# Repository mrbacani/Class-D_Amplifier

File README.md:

# Class-D_Amplifier
Repository for a Class-D amplifier project

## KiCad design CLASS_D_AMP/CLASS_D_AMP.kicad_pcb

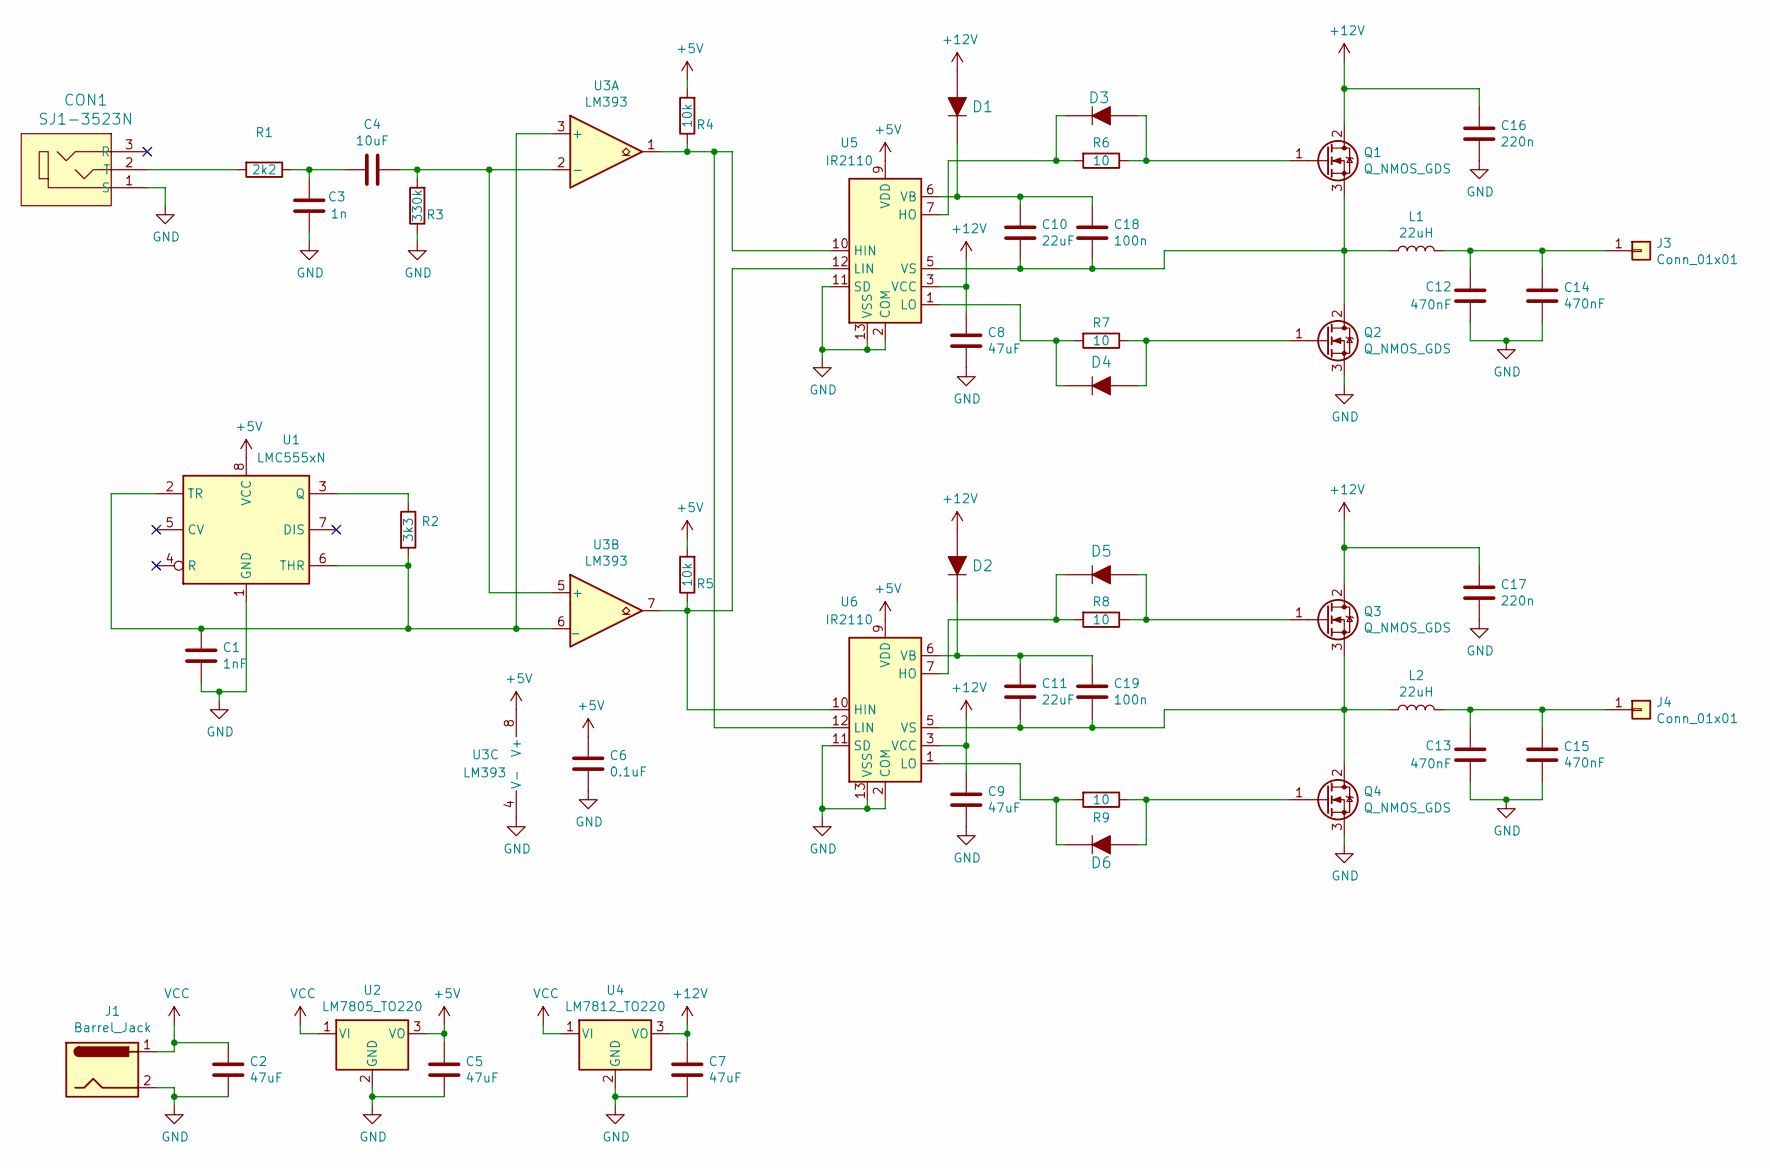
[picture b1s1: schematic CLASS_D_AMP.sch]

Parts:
C1: 1nF; C_1210_3225Metric_Pad1.33x2.70mm_HandSolder
C2, C5, C7, C8, C9: 47uF; C_1210_3225Metric_Pad1.33x2.70mm_HandSolder
C3: 1n; C_1210_3225Metric_Pad1.33x2.70mm_HandSolder
C4: 10uF; C_1210_3225Metric_Pad1.33x2.70mm_HandSolder
C6: 0.1uF; C_1210_3225Metric_Pad1.33x2.70mm_HandSolder
C10, C11: 22uF; C_1210_3225Metric_Pad1.33x2.70mm_HandSolder
C12, C13, C14, C15: 470nF; C_1210_3225Metric_Pad1.33x2.70mm_HandSolder
C16, C17: 220n; C_1210_3225Metric_Pad1.33x2.70mm_HandSolder
C18, C19: 100n; C_1210_3225Metric_Pad1.33x2.70mm_HandSolder
CON1: SJ1-3523N; Headphone_Jack_3.5mm_SJ1-3523N; MPN SJ1-3523N; Digi-Key_PN CP1-3523N-ND
D1, D2, D3, D4, D5, D6: 1N4148X-TP; SOD-523; MPN 1N4148X-TP; Digi-Key_PN 1N4148XTPMSCT-ND
J1: Barrel_Jack; Barrel_Jack_5.5mmODx2.1mmID_PJ-202A
J3, J4: Conn_01x01; PinHeader_1x01_P2.54mm_Vertical
L1, L2: 22uH; L_1210_3225Metric_Pad1.42x2.65mm_HandSolder
Q1, Q2, Q3, Q4: Q_NMOS_GDS; TO-220-3
R1: 2k2; R_1210_3225Metric_Pad1.30x2.65mm_HandSolder
R2: 3k3; R_1210_3225Metric_Pad1.30x2.65mm_HandSolder
R3: 330k; R_1210_3225Metric_Pad1.30x2.65mm_HandSolder
R4, R5: 10k; R_1210_3225Metric_Pad1.30x2.65mm_HandSolder
R6, R7, R8, R9: 10; R_1210_3225Metric_Pad1.30x2.65mm_HandSolder
U1: LMC555xN; DIP-8_W7.62mm
U2: LM7805_TO220; TO-220-3_Vertical
U3: LM393; SOIC-8_W3.9mm
U4: LM7812_TO220; TO-220-3_Vertical
U5, U6: IR2110; DIP-14_W7.62mm

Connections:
+5V: C5.1, C6.1, R4.2, R5.2, U1.8 (VCC), U2.3 (VO), U3.8 (V+), U5.9 (VDD), U6.9 (VDD)
+12V: C7.1, C8.1, C9.1, C16.1, C17.1, D1.A, D2.A, Q1.2 (D), Q3.2 (D), U4.3 (VO), U5.3 (VCC), U6.3 (VCC)
GND: C1.2, C2.2, C3.2, C5.2, C6.2, C7.2, C8.2, C9.2, C12.2, C13.2, C14.2, C15.2, C16.2, C17.2, CON1.1 (S), J1.2, Q2.3 (S), Q4.3 (S), R3.1, U1.1 (GND), U2.2 (GND), U3.4 (V-), U4.2 (GND), U5.2 (COM), U5.11 (SD), U5.13 (VSS), U6.2 (COM), U6.11 (SD), U6.13 (VSS)
unnamed: C1.1, R2.2, U1.2 (TR), U1.6 (THR), U3.3 (+), U3.6 (_)
unnamed: C3.1, C4.2, R1.1
unnamed: C4.1, R3.2, U3.2 (-), U3.5 (+)
unnamed: C10.1, C18.1, D1.K, U5.6 (VB)
unnamed: C10.2, C18.2, L1.1, Q1.3 (S), Q2.2 (D), U5.5 (VS)
unnamed: C11.1, C19.1, D2.K, U6.6 (VB)
unnamed: C11.2, C19.2, L2.1, Q3.3 (S), Q4.2 (D), U6.5 (VS)
unnamed: C12.1, C14.1, J3.1, L1.2
unnamed: C13.1, C15.1, J4.1, L2.2
unnamed: CON1.2 (T), R1.2
unnamed: D3.A, Q1.1 (G), R6.1
unnamed: D3.K, R6.2, U5.7 (HO)
unnamed: D4.A, Q2.1 (G), R7.1
unnamed: D4.K, R7.2, U5.1 (LO)
unnamed: D5.A, Q3.1 (G), R8.1
unnamed: D5.K, R8.2, U6.7 (HO)
unnamed: D6.A, Q4.1 (G), R9.1
unnamed: D6.K, R9.2, U6.1 (LO)
unnamed: R2.1, U1.3 (Q)
unnamed: R4.1, U3.1, U5.10 (HIN), U6.12 (LIN)
unnamed: R5.1, U3.7, U5.12 (LIN), U6.10 (HIN)
VCC: C2.1, J1.1, U2.1 (VI), U4.1 (VI)

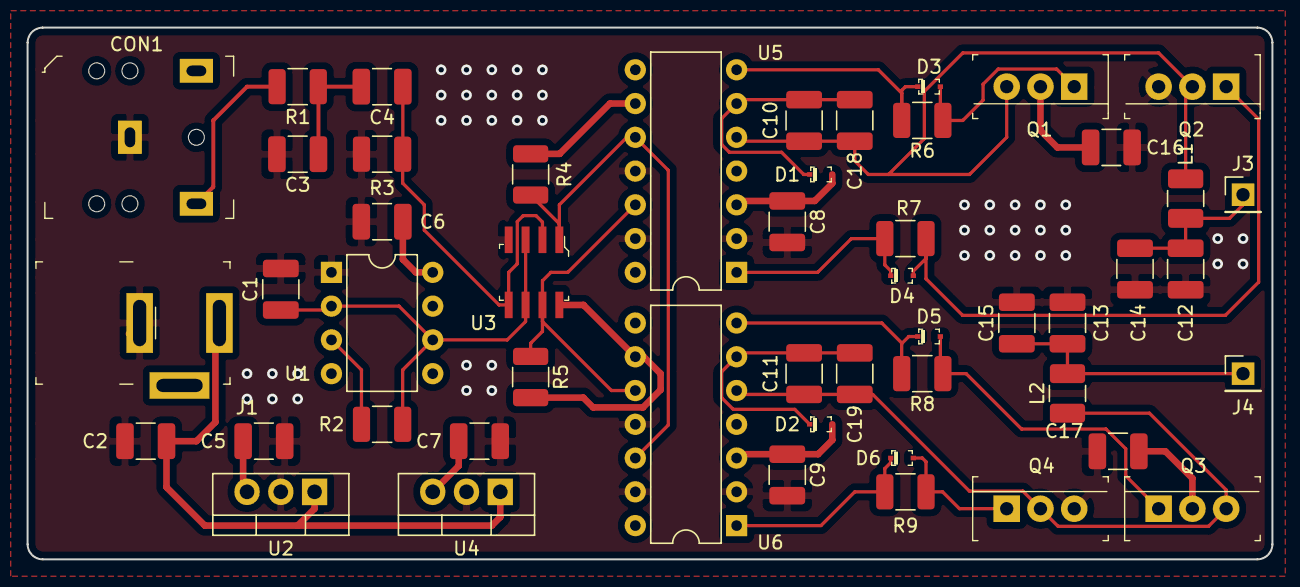
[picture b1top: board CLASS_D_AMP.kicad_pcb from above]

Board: 4 copper layers, 93.6 x 40.0 mm, 50 parts (0 on the bottom side), 25 nets.

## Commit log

2021-05-31 Adding KiCAD files
